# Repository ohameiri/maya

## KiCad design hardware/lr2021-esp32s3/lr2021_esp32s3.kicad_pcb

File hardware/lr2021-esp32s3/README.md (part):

# LR2021 + ESP32-S3 LoRa Plus board

A 4-layer, 62 × 47 mm KiCad 9 board with:

- **Semtech LR2021** LoRa Plus transceiver (QFN-32 5×5). Its matching networks follow Semtech's LR2021 reference design (switchless "direct-tie").
  - Sub-GHz path **868/915 MHz**, up to **+22 dBm** (PA_LF), on SMA **J5**.
  - **2.4 GHz** path, up to **+12 dBm** (PA_HF), on SMA **J6**.
- **ESP32-S3-WROOM-1U-N16R8** module (16 MB flash, 8 MB octal PSRAM, LCSC C3013946). This is the U.FL variant with no PCB antenna, so the board needs no antenna keepout. Wi-Fi/BLE are not used; the U.FL is left unconnected (an antenna can still be clipped on later if needed).
- **USB-C** wired straight to the ESP32-S3 native USB (GPIO19/20). It handles flashing, USB-CDC console and JTAG, with no USB-UART bridge.
- Power from **USB-C 5 V**, a **5 V screw terminal** or a **3.3 V screw terminal**. Any combination can be connected at the same time.
- RESET and BOOT buttons, a power LED, a user LED on GPIO2, and a 2×10 GPIO header.

Everything is generated from the Python scripts in [`scripts/`](scripts), so the design can be reviewed and rebuilt from source.

| | |
|---|---|
|  |  |

### 3D

| | |
|---|---|
|  |  |

The KiCad library has no 3D models for the HRO TYPE-C-31-M-12 USB-C receptacle, the XKB TS-1187A buttons or a 0402 diode. Simplified models built from the datasheet dimensions are generated by [`scripts/gen_3d_models.py`](scripts/gen_3d_models.py) (CadQuery) into `lib/3d/`, and the footprints point to them.

## Power design

### Load budget (from the datasheets)

| Consumer | Typical | Peak | Source |
|---|---|---|---|
| ESP32-S3 (Wi-Fi TX 802.11b, 20.5 dBm; worst case only, the radio is unused) | 95 mA (RX/idle) | **355 mA** | ESP32-S3-WROOM-1/1U datasheet |
| LR2021 TX PA_LF +22 dBm, 915 MHz (SIMO, 3.3 V) | 105 mA | **~120 mA** | LR2021 DS rev 1.1, IDDTXLF1 / Fig 1-3 |
| LR2021 TX PA_HF +12 dBm, 2.4 GHz | 24 mA | 24 mA | LR2021 DS Fig 1-7 |
| LEDs, pull-ups | 3 mA | 3 mA | |
| **Total on +3V3** | ~200 mA | **~480 mA** | |

The 3.3 V rail is sized for **1 A**, about 2× the worst-case peak.

### Topology

```
USB-C VBUS ──B5819W──┐
                     ├── +5V ── AP7361C-33 (1 A LDO) ── +3V3_LDO ── LM66100 ──┐
5V screw terminal ───┴──B5819W (SMF5.0CA TVS on input)                        ├── +3V3 ── ESP32-S3, LR2021 (via ferrite), LEDs
3V3 screw terminal ── +3V3_EXT ───────────────────────────────── LM66100 ──────┘
```

- **5 V inputs**: USB-C and the 5 V terminal are combined by two B5819W Schottky diodes. They block back-feed into the USB host and protect against reverse polarity. The LDO input then sees about 4.5 V.
- **LDO**: Diodes AP7361C-33E (1 A, 340 mV dropout at 1 A, SOT-223 with the GND tab on a ground pour). Worst-case dissipation is (4.55 − 3.3) V × 0.48 A ≈ 0.6 W during short Wi-Fi bursts. The average is about 0.15 W.
- **3.3 V inputs**: The LDO output and the external 3.3 V input are combined by two **TI LM66100** ideal diodes (CE tied to VOUT, the reverse-current-blocking setup in the TI datasheet).
  - The higher source supplies the rail and neither source can back-feed the other.
  - The drop is about 50 mV at 0.5 A (79–125 mΩ), so a 3.3 V input still gives at least 3.2 V.
  - The LM66100 also provides reverse-polarity protection on the 3.3 V terminal.
- **External 3.3 V must stay between 3.0 and 3.6 V.** The ESP32-S3 limit is 3.6 V and the LR2021 operating maximum is 3.7 V (absolute maximum 3.9 V).
- **LR2021 supply**: VBAT gets its own ferrite (FB1) plus 100 nF and 4.7 µF. The internal SIMO DC-DC uses the 2.2 µH LQM18PN2R2 inductor, as Semtech specifies. PA_LF reaches the full +22 dBm for VBAT ≥ 2.2 V.

The schematic has one intentional ERC warning: the two LM66100 outputs (power-out pins) are tied together. The project's pin-conflict matrix downgrades power-out↔power-out from error to warning for that reason.

## RF design

- **Matching values** come from Semtech's LR2021 reference design (e788v01a, 868/915 MHz + 2.4 GHz). PA chokes: 12 nH (LF) and 18 nH (HF). Values on the schematic RF sheet:
  - LF: L 4.7 nH, C 22 pF, C 7.5 pF ∥ (3.9 nH ∥ 1.8 pF), 3.9 pF, 2.4 nH, 1.8 pF.
  - LF RX: 18 pF, 2.2 pF, 24 nH.
  - HF: 1.5 nH, 6.8 pF, 2.7 pF, (1.6 nH ∥ 1.1 pF), 1.2 pF, 1.1 nH, 2.0 pF.
  - HF RX: 18 pF, 2.4 nH.
- **Antenna ESD (D6, D7)**: DOWO PESD0402V12 (LCSC C19626255) on each SMA feed, as in Semtech's reference design. It is 0.05 pF, bidirectional, with a 12 V working voltage, so it does not clip the +22 dBm signal: 4 V peak into 50 Ω, up to about 8 V into a badly matched antenna. Simulated insertion loss is 0.04–0.05 dB.
- **Optional parts (DNP)**: L12 and C33 are tuning pads.
- **Transmission lines**: grounded coplanar waveguide on L1 referenced to the solid **In1 ground plane**. Trace **0.38 mm** with a **0.2 mm** gap gives ≈ 50 Ω on the JLCPCB `JLC04161H-7628` stackup (0.2104 mm prepreg, εr ≈ 4.4).
  - A GND via fence runs along both sides of each feed, with gaps of 1.0–2.4 mm on the long runs (λ/20 at 2.45 GHz is 3.4 mm). [`add_rf_fence.py`](scripts/add_rf_fence.py) adds it after routing, and more stitching vias surround each SMA launch.
- **Layout**: The LR2021 is rotated so all its RF pins face the right board edge. Each band has a TX row and an RX row of 0402 parts, the same structure as Semtech's layout.
  - Shunt parts have their own ground via right at the pad.
  - The RF section was routed by hand and locked. The autorouter was fenced out of it.
- **ESP32 radio**: The WROOM-1U has no PCB antenna, so there is no keepout and the module sits inside the board. With Wi-Fi/BLE disabled in firmware the ESP32 draws about 30–40 mA; the supply is still sized for the radio-on worst case.

> **Tuning note.** Semtech's values were tuned on their own PCB with mostly 0201 parts. This board uses 0402 parts and a different layout, so the match is a good starting point, not a guarantee. Before running full power, check S11 and the TX output with a VNA or spectrum analyzer, and adjust the shunt capacitors if needed.

## ESP32-S3 ↔ LR2021 pin map

| LR2021 | ESP32-S3 | Notes |
|---|---|---|
| NSS | GPIO10 | 10 k pull-up (radio deselected during boot) |
| MOSI | GPIO11 | FSPI IO-MUX pins |
| SCK | GPIO12 | |
| MISO | GPIO13 | |
| NRESET | GPIO14 | |
| BUSY | GPIO21 | |
| DIO9 | GPIO47 | IRQ (map any LR2021 interrupt to it with `SetDioFunction`) |

Only one IRQ line is wired. RadioLib's LR2021 driver needs only an IRQ line plus BUSY.
- DIO5–DIO8, DIO10 and DIO11 are left unconnected. Semtech says unused DIOs can float. The switchless RF design needs no RF-switch control lines.
- Freeing those pins left room around the QFN for a clean hand fanout.

Other ESP32-S3 connections:
- USB D−/D+ go to GPIO19/20 (with USBLC6-2SC6 ESD protection).
- The user LED is on GPIO2. BOOT is GPIO0 and RESET is EN.
- GPIO header J4:

  | Pins | Signals |
  |---|---|
  | 1, 2 | 3V3, 5V |
  | 3–14 | GPIO4, 5, 6, 7, 9, 48, 38, 39, 40, 41, 42, 1 |
  | 15, 16 | U0TXD, U0RXD |
  | 17–20 | GND |

- Not used:
  - GPIO35–37 are taken by the octal PSRAM.
  - The strapping pins GPIO3, GPIO45 and GPIO46 are left free.
  - GPIO8 and GPIO15–18 are unconnected. On the compact board there is no room to route them from the module's left side to the header.

## PCB

- **Size and stackup**: 62 × 47 mm, 4 layers, 1.6 mm, JLCPCB `JLC04161H-7628`.
- **Mounting**: two M2 holes, one on the right edge between the two SMA connectors and one at the top between the ESP32 module and the radio section.

  | Layer | Use |
  |---|---|
  | L1 (F.Cu) | Components, RF, signals, GND pour |
  | L2 (In1) | Solid GND (RF reference) |
  | L3 (In2) | +3V3 plane |
  | L4 (B.Cu) | Signals, GND pour |

- **Hand-routed in [`gen_pcb.py`](scripts/gen_pcb.py)** and locked before autorouting:
  - the RF section;
  - the full LR2021 fanout (crystal, NTC divider, SIMO loop, VBAT/VDCC/VPAX, SPI escape vias);
  - the duplicated USB-C pads;
  - a via from every +3V3/GND pad to its plane.
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
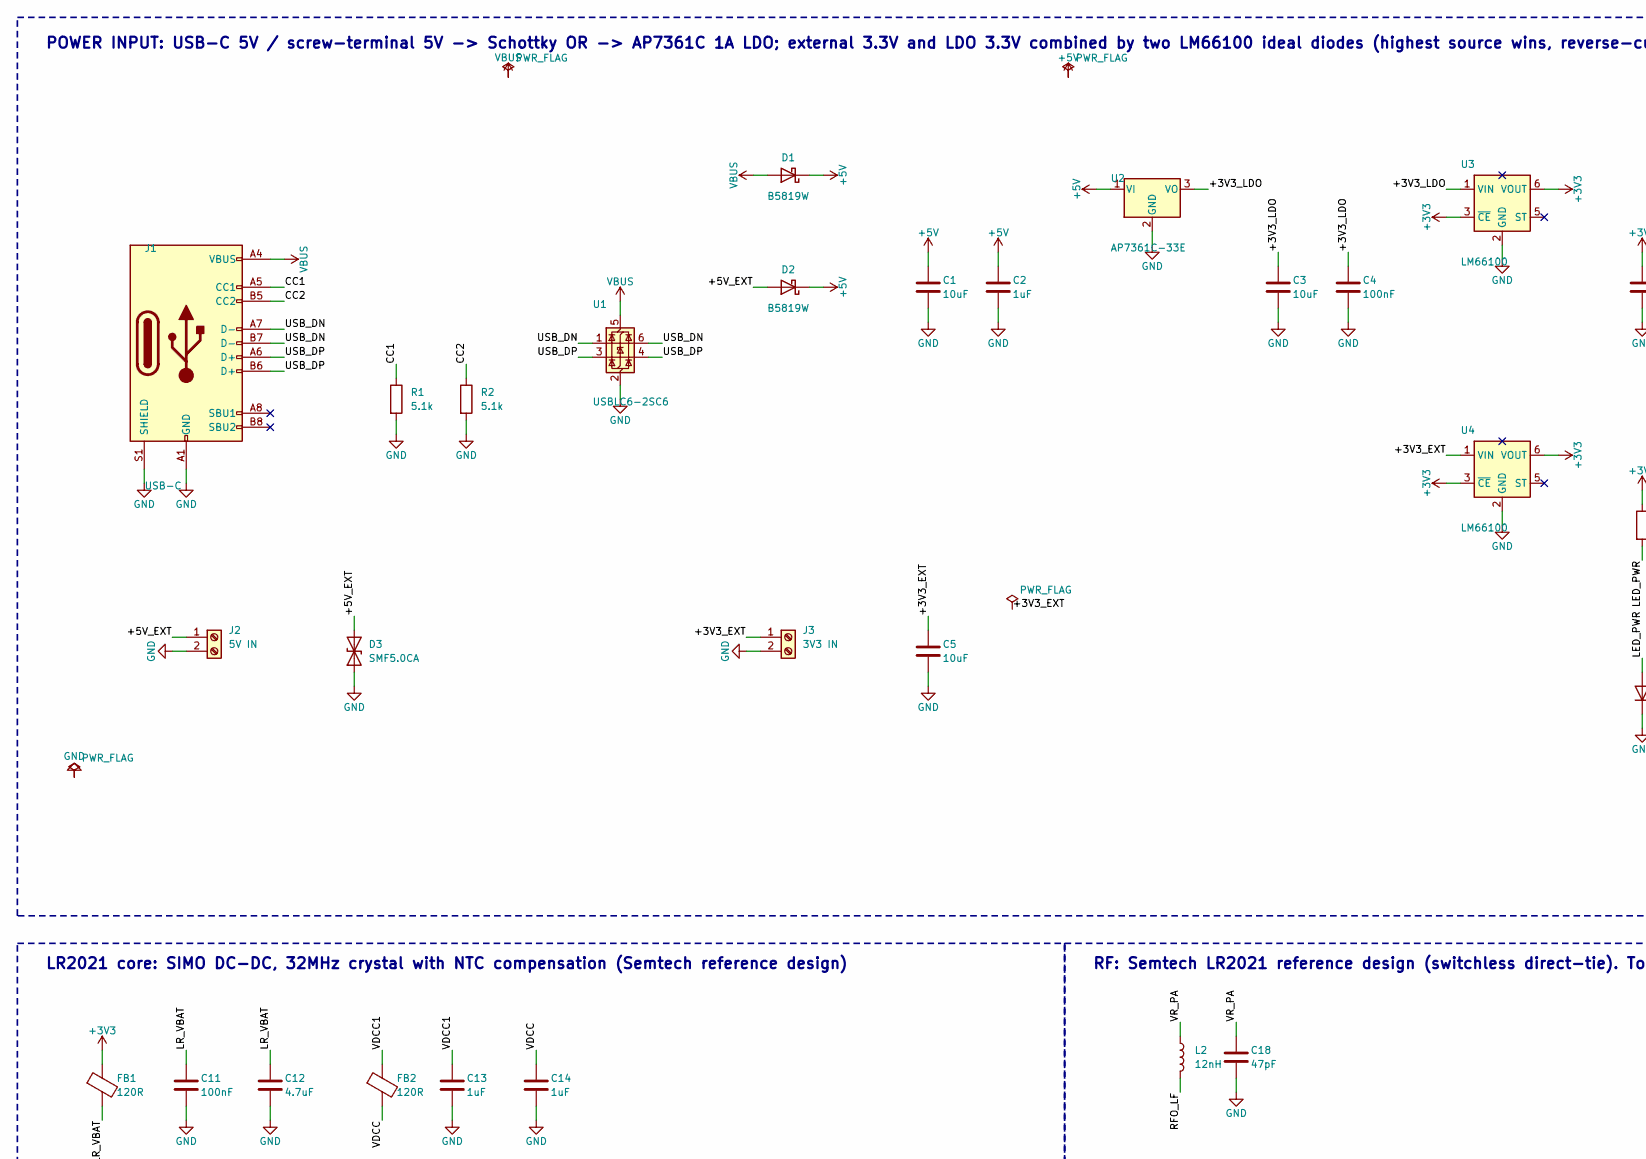
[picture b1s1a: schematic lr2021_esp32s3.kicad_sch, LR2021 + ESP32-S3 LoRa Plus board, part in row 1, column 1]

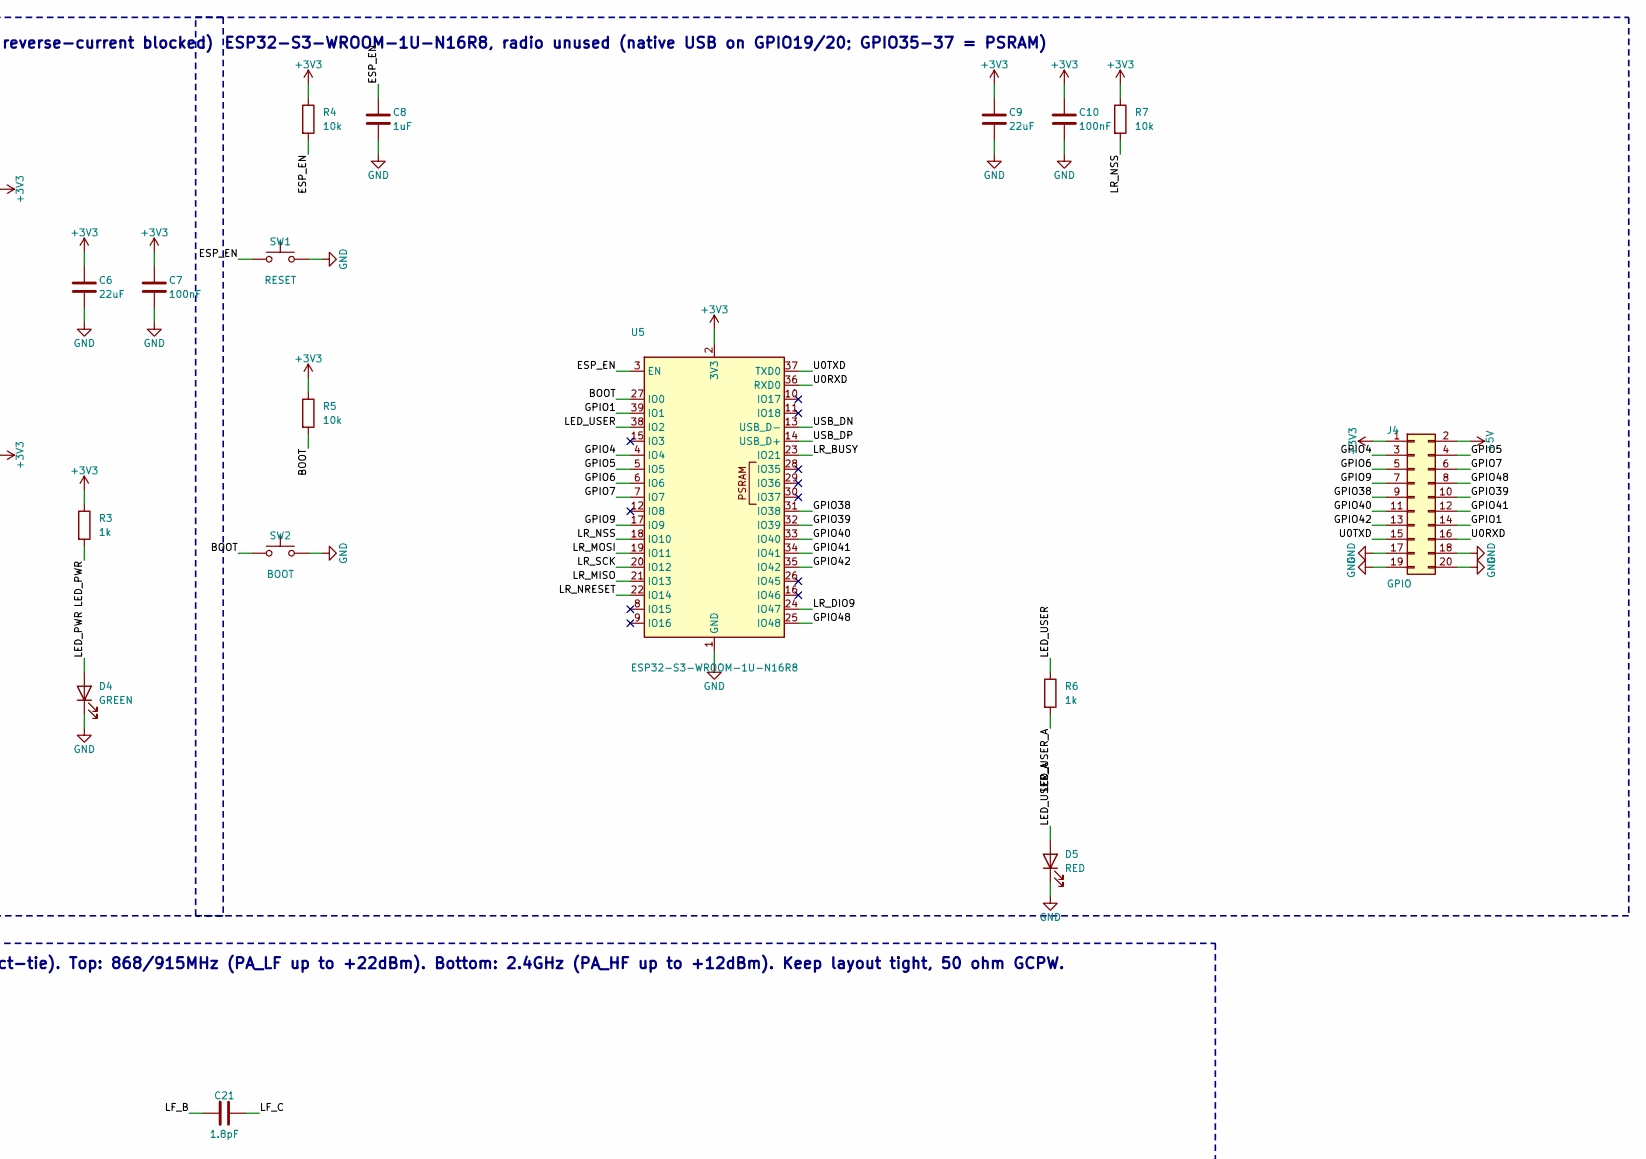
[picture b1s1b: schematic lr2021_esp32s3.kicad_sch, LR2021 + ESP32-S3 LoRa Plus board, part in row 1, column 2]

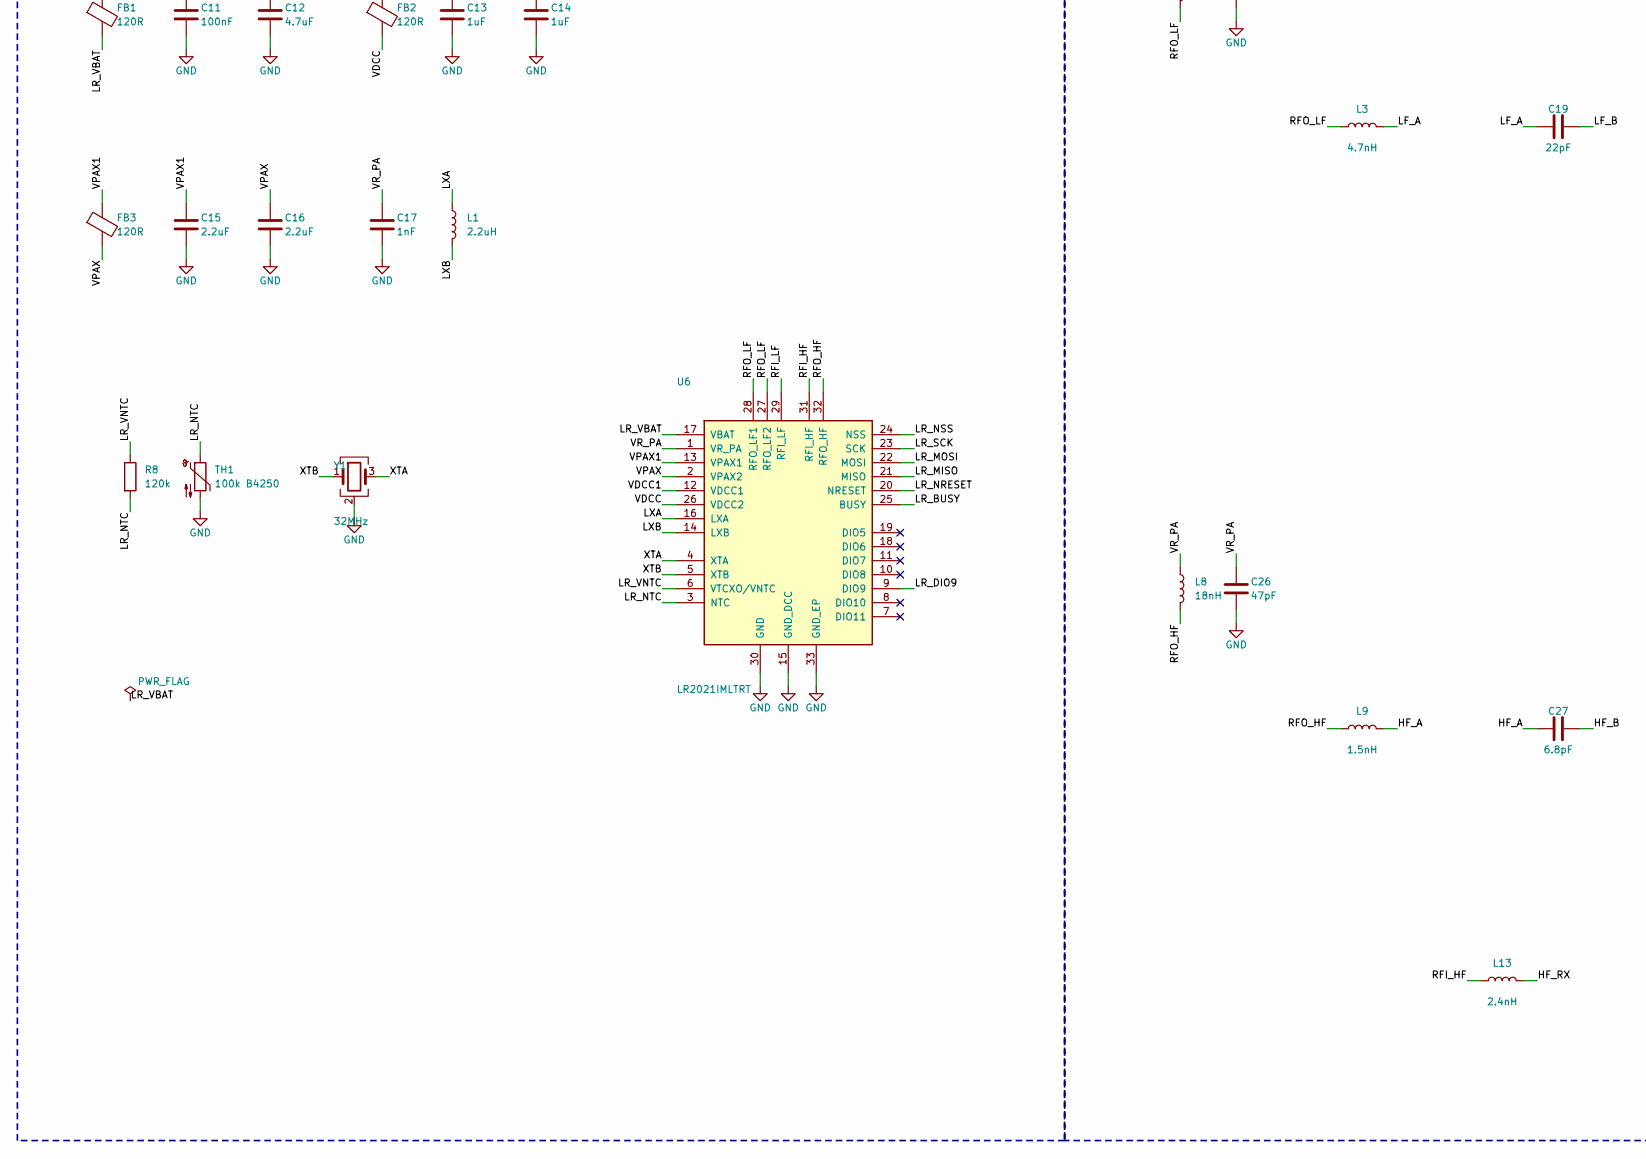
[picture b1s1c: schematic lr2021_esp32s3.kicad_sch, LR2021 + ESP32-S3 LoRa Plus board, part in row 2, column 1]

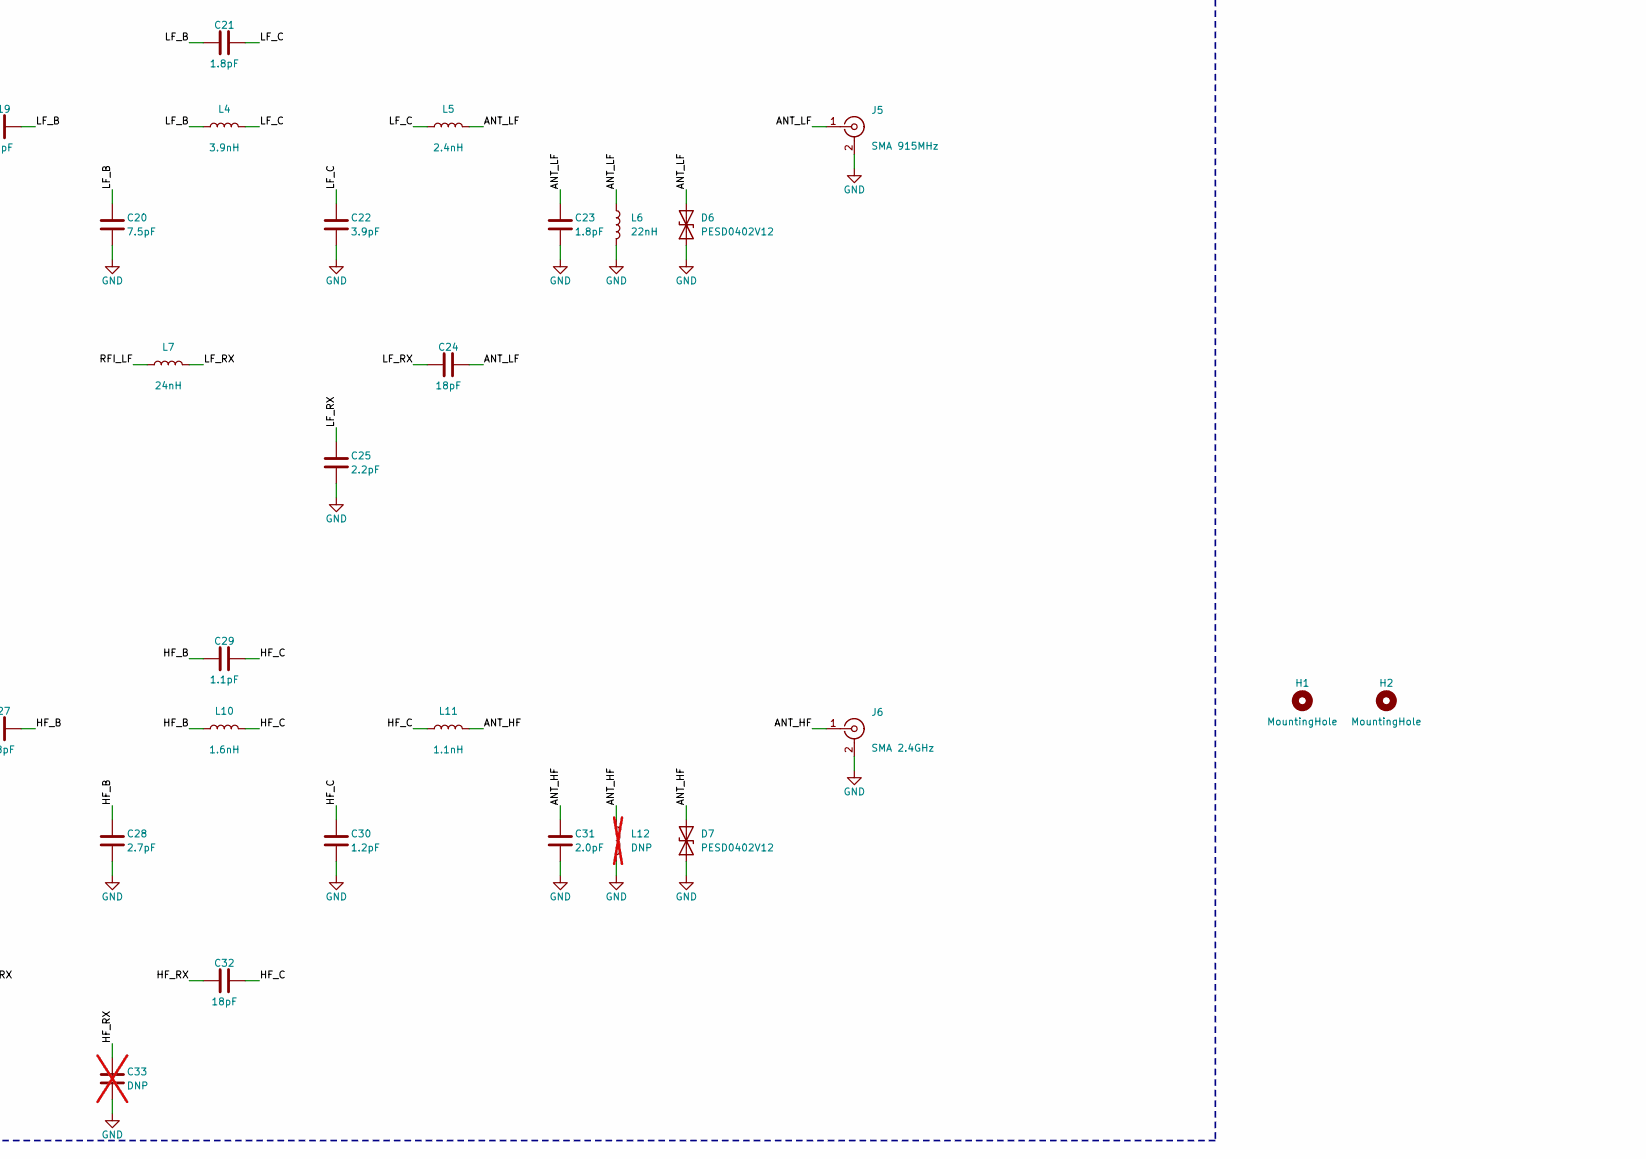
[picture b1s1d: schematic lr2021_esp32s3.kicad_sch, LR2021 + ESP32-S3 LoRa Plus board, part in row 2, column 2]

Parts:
C1, C3, C5: 10uF; C_0805_2012Metric; MPN CL21A106KAYNNNE; LCSC C15850
C2, C8, C13, C14: 1uF; C_0402_1005Metric; MPN CL05A105KA5NQNC; LCSC C52923
C4, C7, C10, C11: 100nF; C_0402_1005Metric; MPN CL05B104KO5NNNC; LCSC C1525
C6, C9: 22uF; C_0805_2012Metric; MPN CL21A226MAQNNNE; LCSC C45783
C12: 4.7uF; C_0402_1005Metric; MPN CL05A475MP5NRNC; LCSC C23733
C15, C16: 2.2uF; C_0402_1005Metric; MPN CL05A225KP5NSNC; LCSC C107369
C17: 1nF; C_0402_1005Metric; MPN 0402B102K500NT; LCSC C1523
C18, C26: 47pF; C_0402_1005Metric; MPN CC0402JRNPO9BN470; LCSC C60137
C19: 22pF; C_0402_1005Metric; MPN 0402CG220J500NT; LCSC C1555
C20: 7.5pF; C_0402_1005Metric; MPN CQ0402BRNPO9BN7R5; LCSC C1855318
C21, C23: 1.8pF; C_0402_1005Metric; MPN CC0402BRNPO9BN1R8; LCSC C327209
C22: 3.9pF; C_0402_1005Metric; MPN CC0402BRNPO9BN3R9; LCSC C505474
C24, C32: 18pF; C_0402_1005Metric; MPN 0402CG180J500NT; LCSC C1549
C25: 2.2pF; C_0402_1005Metric; MPN CC0402BRNPO9BN2R2; LCSC C325452
C27: 6.8pF; C_0402_1005Metric; MPN CC0402BRNPO9BN6R8; LCSC C327291
C28: 2.7pF; C_0402_1005Metric; MPN CC0402BRNPO9BN2R7; LCSC C326937
C29: 1.1pF; C_0402_1005Metric; MPN RF15N1R1B500CT; LCSC C180259
C30: 1.2pF; C_0402_1005Metric; MPN CC0402BRNPO9BN1R2; LCSC C327292
C31: 2.0pF; C_0402_1005Metric; MPN CC0402BRNPO9BN2R0; LCSC C281756
C33: DNP; C_0402_1005Metric; not fitted
D1, D2: B5819W; D_SOD-123; MPN B5819W; LCSC C8598
D3: SMF5.0CA; D_SOD-123F; MPN SMF5.0CA; LCSC C2980402
D4: GREEN; LED_0603_1608Metric; MPN LTST-C190KGKT; LCSC C125094
D5: RED; LED_0603_1608Metric; MPN KT-0603R; LCSC C2286
D6, D7: PESD0402V12; D_0402_1005Metric; MPN PESD0402V12; LCSC C19626255
FB1, FB2, FB3: 120R; L_0402_1005Metric; MPN BLM15AG121SN1D; LCSC C85812
H1, H2: MountingHole; MountingHole_2.2mm_M2
J1: USB-C; USB_C_Receptacle_HRO_TYPE-C-31-M-12; MPN HRO TYPE-C-31-M-12; LCSC C165948
J2: 5V IN; TerminalBlock_Phoenix_MKDS-1,5-2_1x02_P5.00mm_Horizontal; MPN KF301-5.0-2P; LCSC C474881
J3: 3V3 IN; TerminalBlock_Phoenix_MKDS-1,5-2_1x02_P5.00mm_Horizontal; MPN KF301-5.0-2P; LCSC C474881
J4: GPIO; PinHeader_2x10_P2.54mm_Vertical; MPN HX PZ2.54-2x10P ZZ; LCSC C42372518
J5: SMA 915MHz; SMA_Samtec_SMA-J-P-H-ST-EM1_EdgeMount; MPN SMA-J-P-H-ST-EM1; LCSC C5199907
J6: SMA 2.4GHz; SMA_Samtec_SMA-J-P-H-ST-EM1_EdgeMount; MPN SMA-J-P-H-ST-EM1; LCSC C5199907
L1: 2.2uH; L_0603_1608Metric; MPN LQM18PN2R2MFRL; LCSC C337910
L2: 12nH; L_0402_1005Metric; MPN LQW15AN12NG00D; LCSC C86128
L3: 4.7nH; L_0402_1005Metric; MPN LQW15AN4N7B00D; LCSC C98064
L4: 3.9nH; L_0402_1005Metric; MPN LQW15AN3N9B00D; LCSC C98062
L5, L13: 2.4nH; L_0402_1005Metric; MPN LQW15AN2N4B00D; LCSC C113113
L6: 22nH; L_0402_1005Metric; MPN LQW15AN22NG00D; LCSC C86129
L7: 24nH; L_0402_1005Metric; MPN LQW15AN24NG00D; LCSC C167472
L8: 18nH; L_0402_1005Metric; MPN LQW15AN18NG00D; LCSC C91622
L9: 1.5nH; L_0402_1005Metric; MPN LQW15AN1N5B00D; LCSC C18221
L10: 1.6nH; L_0402_1005Metric; MPN MWSD1005C1N6STM01; LCSC C778760
L11: 1.1nH; L_0402_1005Metric; MPN MHQ1005P1N1BT000; LCSC C1332701
L12: DNP; L_0402_1005Metric; not fitted
R1, R2: 5.1k; R_0402_1005Metric; MPN 0402WGF5101TCE; LCSC C25905
R3, R6: 1k; R_0402_1005Metric; MPN 0402WGF1001TCE; LCSC C11702
R4, R5, R7: 10k; R_0402_1005Metric; MPN 0402WGF1002TCE; LCSC C25744
R8: 120k; R_0402_1005Metric; MPN 0402WGF1203TCE; LCSC C25750
SW1: RESET; SW_Push_1P1T_XKB_TS-1187A; MPN TS-1187A-B-A-B; LCSC C318884
SW2: BOOT; SW_Push_1P1T_XKB_TS-1187A; MPN TS-1187A-B-A-B; LCSC C318884
TH1: 100k B4250; R_0402_1005Metric; MPN NCP15WF104F03RC; LCSC C77130
U1: USBLC6-2SC6; SOT-23-6; MPN USBLC6-2SC6; LCSC C7519
U2: AP7361C-33E; SOT-223-3_TabPin2; MPN AP7361C-33E-13; LCSC C500795
U3, U4: LM66100; SOT-363_SC-70-6; MPN LM66100DCKR; LCSC C2869734
U5: ESP32-S3-WROOM-1U-N16R8; ESP32-S3-WROOM-1U; MPN ESP32-S3-WROOM-1U-N16R8; LCSC C3013946
U6: LR2021IMLTRT; QFN-32-1EP_5x5mm_P0.5mm_EP3.7x3.7mm_ThermalVias; MPN LR2021IMLTRT; LCSC C49421489
Y1: 32MHz; Crystal_SMD_2016-4Pin_2.0x1.6mm; MPN NX2016SA-32M-EXS00A-CS06465; LCSC C1986260

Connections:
+3V3: C6.1, C7.1, C9.1, C10.1, FB1.1, J4.1, R3.1, R4.1, R5.1, R7.1, U3.3 (~CE), U3.6 (VOUT), U4.3 (~CE), U4.6 (VOUT), U5.2 (3V3)
+5V: C1.1, C2.1, D1.1 (K), D2.1 (K), J4.2, U2.1 (VI)
/+3V3_EXT: C5.1, J3.1, U4.1 (VIN)
/+3V3_LDO: C3.1, C4.1, U2.3 (VO), U3.1 (VIN)
/+5V_EXT: D2.2 (A), D3.2 (A2), J2.1
/ANT_HF: C31.1, D7.2 (A2), J6.1 (In), L11.2, L12.1
/ANT_LF: C23.1, C24.2, D6.2 (A2), J5.1 (In), L5.2, L6.1
/BOOT: R5.2, SW2.1, U5.27 (IO0)
/CC1: J1.A5 (CC1), R1.1
/CC2: J1.B5 (CC2), R2.1
/ESP_EN: C8.1, R4.2, SW1.1, U5.3 (EN)
/GPIO1: J4.14, U5.39 (IO1)
/GPIO4: J4.3, U5.4 (IO4)
/GPIO5: J4.4, U5.5 (IO5)
/GPIO6: J4.5, U5.6 (IO6)
/GPIO7: J4.6, U5.7 (IO7)
/GPIO9: J4.7, U5.17 (IO9)
/GPIO38: J4.9, U5.31 (IO38)
/GPIO39: J4.10, U5.32 (IO39)
/GPIO40: J4.11, U5.33 (IO40)
/GPIO41: J4.12, U5.34 (IO41)
/GPIO42: J4.13, U5.35 (IO42)
/GPIO48: J4.8, U5.25 (IO48)
/HF_A: C27.1, L9.2
/HF_B: C27.2, C28.1, C29.1, L10.1
/HF_C: C29.2, C30.1, C32.2, L10.2, L11.1
/HF_RX: C32.1, C33.1, L13.2
/LED_PWR: D4.2 (A), R3.2
/LED_USER: R6.1, U5.38 (IO2)
/LED_USER_A: D5.2 (A), R6.2
/LF_A: C19.1, L3.2
/LF_B: C19.2, C20.1, C21.1, L4.1
/LF_C: C21.2, C22.1, L4.2, L5.1
/LF_RX: C24.1, C25.1, L7.2
/LR_BUSY: U5.23 (IO21), U6.25 (BUSY)
/LR_DIO9: U5.24 (IO47), U6.9 (DIO9)
/LR_MISO: U5.21 (IO13), U6.21 (MISO)
/LR_MOSI: U5.19 (IO11), U6.22 (MOSI)
/LR_NRESET: U5.22 (IO14), U6.20 (NRESET)
/LR_NSS: R7.2, U5.18 (IO10), U6.24 (NSS)
/LR_NTC: R8.2, TH1.1, U6.3 (NTC)
/LR_SCK: U5.20 (IO12), U6.23 (SCK)
/LR_VBAT: C11.1, C12.1, FB1.2, U6.17 (VBAT)
/LR_VNTC: R8.1, U6.6 (VTCXO/VNTC)
/LXA: L1.1, U6.16 (LXA)
/LXB: L1.2, U6.14 (LXB)
/RFI_HF: L13.1, U6.31 (RFI_HF)
/RFI_LF: L7.1, U6.29 (RFI_LF)
/RFO_HF: L8.2, L9.1, U6.32 (RFO_HF)
/RFO_LF: L2.2, L3.1, U6.27 (RFO_LF2), U6.28 (RFO_LF1)
/U0RXD: J4.16, U5.36 (RXD0)
/U0TXD: J4.15, U5.37 (TXD0)
/USB_DN: J1.A7 (D-), J1.B7 (D-), U1.1 (I/O1), U1.6 (I/O1), U5.13 (USB_D-)
/USB_DP: J1.A6 (D+), J1.B6 (D+), U1.3 (I/O2), U1.4 (I/O2), U5.14 (USB_D+)
/VDCC: C14.1, FB2.2, U6.26 (VDCC2)
/VDCC1: C13.1, FB2.1, U6.12 (VDCC1)
/VPAX: C16.1, FB3.2, U6.2 (VPAX2)
/VPAX1: C15.1, FB3.1, U6.13 (VPAX1)
/VR_PA: C17.1, C18.1, C26.1, L2.1, L8.1, U6.1 (VR_PA)
/XTA: U6.4 (XTA), Y1.3
/XTB: U6.5 (XTB), Y1.1
GND: C1.2, C2.2, C3.2, C4.2, C5.2, C6.2, C7.2, C8.2, C9.2, C10.2, C11.2, C12.2, C13.2, C14.2, C15.2, C16.2, C17.2, C18.2, C20.2, C22.2, C23.2, C25.2, C26.2, C28.2, C30.2, C31.2, C33.2, D3.1 (A1), D4.1 (K), D5.1 (K), D6.1 (A1), D7.1 (A1), J1.A1 (GND), J1.A12 (GND), J1.B1 (GND), J1.B12 (GND), J1.S1 (SHIELD), J2.2, J3.2, J4.17, J4.18, J4.19, J4.20, J5.2 (Ext), J6.2 (Ext), L6.2, L12.2, R1.2, R2.2, SW1.2, SW2.2, TH1.2, U1.2 (GND), U2.2 (GND), U3.2 (GND), U4.2 (GND), U5.1 (GND), U5.40 (GND), U5.41 (GND), U6.15 (GND_DCC), U6.30 (GND), U6.33 (GND_EP), Y1.2 (G), Y1.4 (G)
VBUS: D1.2 (A), J1.A4 (VBUS), J1.A9 (VBUS), J1.B4 (VBUS), J1.B9 (VBUS), U1.5 (VBUS)

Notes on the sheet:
POWER INPUT: USB-C 5V / screw-terminal 5V -> Schottky OR -> AP7361C 1A LDO; external 3.3V and LDO 3.3V combined by two LM66100 ideal diodes (highest source wins, reverse-current blocked)
ESP32-S3-WROOM-1U-N16R8, radio unused (native USB on GPIO19/20; GPIO35-37 = PSRAM)
LR2021 core: SIMO DC-DC, 32MHz crystal with NTC compensation (Semtech reference design)
RF: Semtech LR2021 reference design (switchless direct-tie). Top: 868/915MHz (PA_LF up to +22dBm). Bottom: 2.4GHz (PA_HF up to +12dBm). Keep layout tight, 50 ohm GCPW.

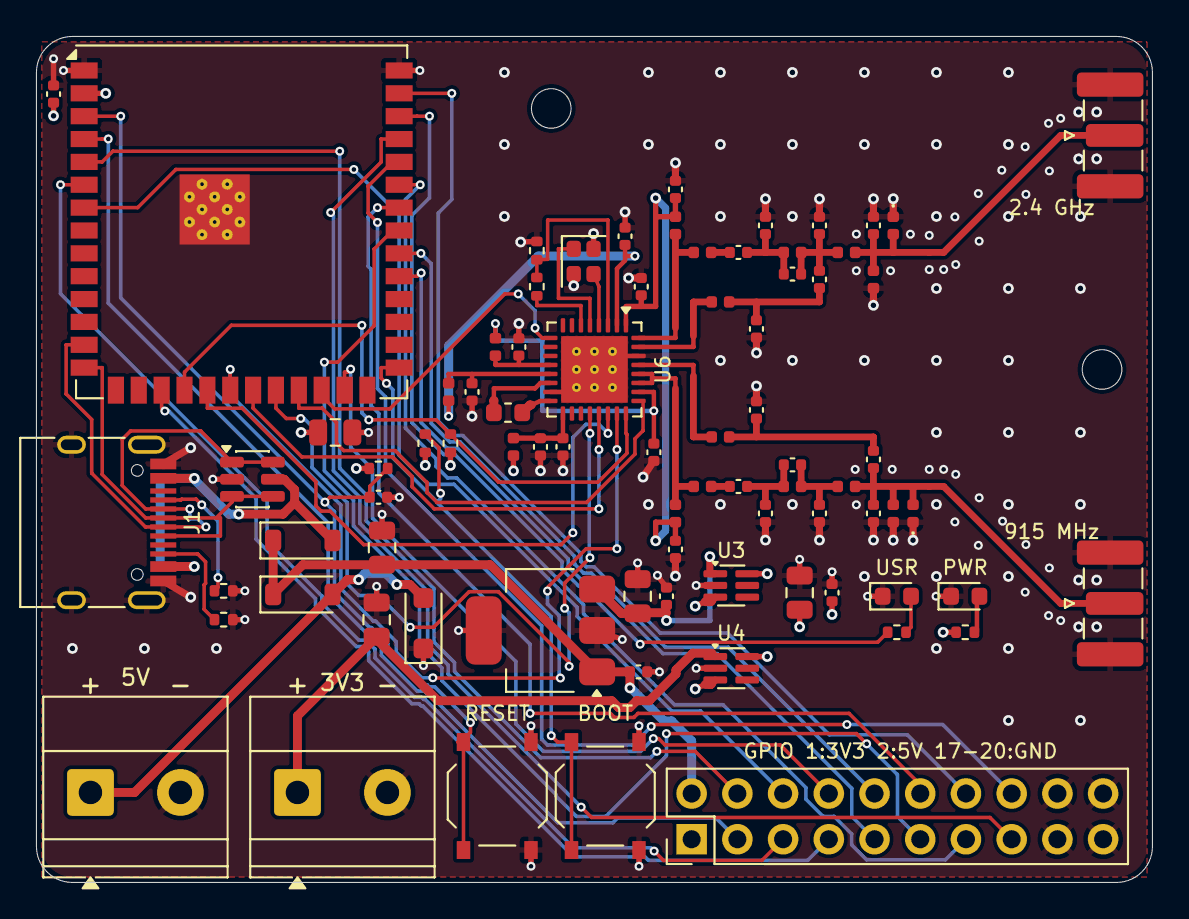
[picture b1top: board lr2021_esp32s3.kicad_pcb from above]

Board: 4 copper layers, 62.0 x 47.0 mm, 82 parts (0 on the bottom side), 63 nets.

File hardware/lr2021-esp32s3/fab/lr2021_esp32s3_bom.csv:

Qty,References,Value,Description,Footprint,MPN,LCSC,Notes,Populate
3,C1 C3 C5,10uF,10uF 16V X5R 0805,C_0805_2012Metric,CL21A106KAYNNNE,C15850,,yes
4,C2 C8 C13 C14,1uF,1uF 10V X5R 0402,C_0402_1005Metric,CL05A105KA5NQNC,C52923,,yes
4,C4 C7 C10 C11,100nF,100nF 16V X7R 0402,C_0402_1005Metric,CL05B104KO5NNNC,C1525,,yes
2,C6 C9,22uF,22uF 16V X5R 0805,C_0805_2012Metric,CL21A226MAQNNNE,C45783,,yes
1,C12,4.7uF,4.7uF 10V X5R 0402,C_0402_1005Metric,CL05A475MP5NRNC,C23733,,yes
2,C15 C16,2.2uF,2.2uF 10V X5R 0402,C_0402_1005Metric,CL05A225KP5NSNC,C107369,,yes
1,C17,1nF,1nF 16V X7R 0402,C_0402_1005Metric,0402B102K500NT,C1523,,yes
2,C18 C26,47pF,47pF 50V C0G/NP0 0402,C_0402_1005Metric,CC0402JRNPO9BN470,C60137,"C0G/NP0, +/-0.1pF (<10pF) or 2%, Murata GRM15/GJM15 high-Q",yes
1,C19,22pF,22pF 50V C0G/NP0 0402,C_0402_1005Metric,0402CG220J500NT,C1555,"C0G/NP0, +/-0.1pF (<10pF) or 2%, Murata GRM15/GJM15 high-Q",yes
1,C20,7.5pF,7.5pF 50V C0G/NP0 0402,C_0402_1005Metric,CQ0402BRNPO9BN7R5,C1855318,"C0G/NP0, +/-0.1pF (<10pF) or 2%, Murata GRM15/GJM15 high-Q",yes
2,C21 C23,1.8pF,1.8pF 50V C0G/NP0 0402,C_0402_1005Metric,CC0402BRNPO9BN1R8,C327209,"C0G/NP0, +/-0.1pF (<10pF) or 2%, Murata GRM15/GJM15 high-Q",yes
1,C22,3.9pF,3.9pF 50V C0G/NP0 0402,C_0402_1005Metric,CC0402BRNPO9BN3R9,C505474,"C0G/NP0, +/-0.1pF (<10pF) or 2%, Murata GRM15/GJM15 high-Q",yes
2,C24 C32,18pF,18pF 50V C0G/NP0 0402,C_0402_1005Metric,0402CG180J500NT,C1549,"C0G/NP0, +/-0.1pF (<10pF) or 2%, Murata GRM15/GJM15 high-Q",yes
1,C25,2.2pF,2.2pF 50V C0G/NP0 0402,C_0402_1005Metric,CC0402BRNPO9BN2R2,C325452,"C0G/NP0, +/-0.1pF (<10pF) or 2%, Murata GRM15/GJM15 high-Q",yes
1,C27,6.8pF,6.8pF 50V C0G/NP0 0402,C_0402_1005Metric,CC0402BRNPO9BN6R8,C327291,"C0G/NP0, +/-0.1pF (<10pF) or 2%, Murata GRM15/GJM15 high-Q",yes
1,C28,2.7pF,2.7pF 50V C0G/NP0 0402,C_0402_1005Metric,CC0402BRNPO9BN2R7,C326937,"C0G/NP0, +/-0.1pF (<10pF) or 2%, Murata GRM15/GJM15 high-Q",yes
1,C29,1.1pF,1.1pF 50V C0G/NP0 0402,C_0402_1005Metric,RF15N1R1B500CT,C180259,"C0G/NP0, +/-0.1pF (<10pF) or 2%, Murata GRM15/GJM15 high-Q",yes
1,C30,1.2pF,1.2pF 50V C0G/NP0 0402,C_0402_1005Metric,CC0402BRNPO9BN1R2,C327292,"C0G/NP0, +/-0.1pF (<10pF) or 2%, Murata GRM15/GJM15 high-Q",yes
1,C31,2.0pF,2.0pF 50V C0G/NP0 0402,C_0402_1005Metric,CC0402BRNPO9BN2R0,C281756,"C0G/NP0, +/-0.1pF (<10pF) or 2%, Murata GRM15/GJM15 high-Q",yes
1,C33,DNP,DNP 10V X5R 0402,C_0402_1005Metric,,,"C0G/NP0, +/-0.1pF (<10pF) or 2%, Murata GRM15/GJM15 high-Q",DNP
2,D1 D2,B5819W,B5819W,D_SOD-123,B5819W,C8598,,yes
1,D3,SMF5.0CA,SMF5.0CA,D_SOD-123F,SMF5.0CA,C2980402,,yes
1,D4,GREEN,GREEN,LED_0603_1608Metric,LTST-C190KGKT,C125094,,yes
1,D5,RED,RED,LED_0603_1608Metric,KT-0603R,C2286,,yes
2,D6 D7,PESD0402V12,PESD0402V12,D_0402_1005Metric,PESD0402V12,C19626255,"Antenna ESD, 0.05pF, bidirectional, Vrwm 12V (Semtech ref populates this)",yes
3,FB1 FB2 FB3,120R,120R,L_0402_1005Metric,BLM15AG121SN1D,C85812,,yes
1,J1,USB-C,USB-C,USB_C_Receptacle_HRO_TYPE-C-31-M-12,HRO TYPE-C-31-M-12,C165948,,yes
1,J2,5V IN,5V IN,"TerminalBlock_Phoenix_MKDS-1,5-2_1x02_P5.00mm_Horizontal",KF301-5.0-2P,C474881,,yes
1,J3,3V3 IN,3V3 IN,"TerminalBlock_Phoenix_MKDS-1,5-2_1x02_P5.00mm_Horizontal",KF301-5.0-2P,C474881,,yes
1,J4,GPIO,GPIO,PinHeader_2x10_P2.54mm_Vertical,HX PZ2.54-2x10P ZZ,C42372518,,yes
1,J5,SMA 915MHz,SMA 915MHz,SMA_Samtec_SMA-J-P-H-ST-EM1_EdgeMount,SMA-J-P-H-ST-EM1,C5199907,"SMA female edge mount, 1.6mm PCB",yes
1,J6,SMA 2.4GHz,SMA 2.4GHz,SMA_Samtec_SMA-J-P-H-ST-EM1_EdgeMount,SMA-J-P-H-ST-EM1,C5199907,"SMA female edge mount, 1.6mm PCB",yes
1,L1,2.2uH,2.2uH,L_0603_1608Metric,LQM18PN2R2MFRL,C337910,"SIMO inductor: DCR<0.5R, Isat>200mA, SRF>20MHz",yes
1,L2,12nH,12nH,L_0402_1005Metric,LQW15AN12NG00D,C86128,"Wire-wound high-Q, +/-2% or +/-0.1nH, Murata LQW15AN series",yes
1,L3,4.7nH,4.7nH,L_0402_1005Metric,LQW15AN4N7B00D,C98064,"Wire-wound high-Q, +/-2% or +/-0.1nH, Murata LQW15AN series",yes
1,L4,3.9nH,3.9nH,L_0402_1005Metric,LQW15AN3N9B00D,C98062,"Wire-wound high-Q, +/-2% or +/-0.1nH, Murata LQW15AN series",yes
2,L5 L13,2.4nH,2.4nH,L_0402_1005Metric,LQW15AN2N4B00D,C113113,"Wire-wound high-Q, +/-2% or +/-0.1nH, Murata LQW15AN series",yes
1,L6,22nH,22nH,L_0402_1005Metric,LQW15AN22NG00D,C86129,"Wire-wound high-Q, +/-2% or +/-0.1nH, Murata LQW15AN series",yes
1,L7,24nH,24nH,L_0402_1005Metric,LQW15AN24NG00D,C167472,"Wire-wound high-Q, +/-2% or +/-0.1nH, Murata LQW15AN series",yes
1,L8,18nH,18nH,L_0402_1005Metric,LQW15AN18NG00D,C91622,"Wire-wound high-Q, +/-2% or +/-0.1nH, Murata LQW15AN series",yes
1,L9,1.5nH,1.5nH,L_0402_1005Metric,LQW15AN1N5B00D,C18221,"Wire-wound high-Q, +/-2% or +/-0.1nH, Murata LQW15AN series",yes
1,L10,1.6nH,1.6nH,L_0402_1005Metric,MWSD1005C1N6STM01,C778760,"Wire-wound high-Q, +/-2% or +/-0.1nH, Murata LQW15AN series",yes
1,L11,1.1nH,1.1nH,L_0402_1005Metric,MHQ1005P1N1BT000,C1332701,"Wire-wound high-Q, +/-2% or +/-0.1nH, Murata LQW15AN series",yes
1,L12,DNP,DNP,L_0402_1005Metric,,,"Wire-wound high-Q, +/-2% or +/-0.1nH, Murata LQW15AN series",DNP
2,R1 R2,5.1k,5.1k 1% 0402,R_0402_1005Metric,0402WGF5101TCE,C25905,,yes
2,R3 R6,1k,1k 1% 0402,R_0402_1005Metric,0402WGF1001TCE,C11702,,yes
3,R4 R5 R7,10k,10k 1% 0402,R_0402_1005Metric,0402WGF1002TCE,C25744,,yes
1,R8,120k,120k 1% 0402,R_0402_1005Metric,0402WGF1203TCE,C25750,,yes
1,SW1,RESET,RESET,SW_Push_1P1T_XKB_TS-1187A,TS-1187A-B-A-B,C318884,,yes
1,SW2,BOOT,BOOT,SW_Push_1P1T_XKB_TS-1187A,TS-1187A-B-A-B,C318884,,yes
1,TH1,100k B4250,100k B4250,R_0402_1005Metric,NCP15WF104F03RC,C77130,,yes
1,U1,USBLC6-2SC6,USBLC6-2SC6,SOT-23-6,USBLC6-2SC6,C7519,,yes
1,U2,AP7361C-33E,AP7361C-33E,SOT-223-3_TabPin2,AP7361C-33E-13,C500795,,yes
2,U3 U4,LM66100,LM66100,SOT-363_SC-70-6,LM66100DCKR,C2869734,,yes
1,U5,ESP32-S3-WROOM-1U-N16R8,ESP32-S3-WROOM-1U-N16R8,ESP32-S3-WROOM-1U,ESP32-S3-WROOM-1U-N16R8,C3013946,,yes
1,U6,LR2021IMLTRT,LR2021IMLTRT,QFN-32-1EP_5x5mm_P0.5mm_EP3.7x3.7mm_ThermalVias,LR2021IMLTRT,C49421489,,yes
1,Y1,32MHz,32MHz,Crystal_SMD_2016-4Pin_2.0x1.6mm,NX2016SA-32M-EXS00A-CS06465,C1986260,"32MHz, CL=10pF, +/-10ppm, ESR<60R (2016)",yes

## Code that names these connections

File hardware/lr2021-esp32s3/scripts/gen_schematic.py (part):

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ESP_NETS = {
    '2': '+3V3', '1': 'GND', '40': 'GND', '41': 'GND', '3': 'ESP_EN', '27': 'BOOT',
    '13': 'USB_DN', '14': 'USB_DP',
    '17': 'GPIO9', '18': 'LR_NSS', '19': 'LR_MOSI', '20': 'LR_SCK', '21': 'LR_MISO', '22': 'LR_NRESET',
    '23': 'LR_BUSY', '24': 'LR_DIO9', '25': 'GPIO48', '12': NC, '38': 'LED_USER',
    '39': 'GPIO1', '4': 'GPIO4', '5': 'GPIO5', '6': 'GPIO6', '7': 'GPIO7', '8': NC, '9': NC,
    '10': NC, '11': NC, '31': 'GPIO38', '32': 'GPIO39', '33': 'GPIO40', '34': 'GPIO41',
    '35': 'GPIO42', '37': 'U0TXD', '36': 'U0RXD',
    '15': NC, '16': NC, '26': NC, '28': NC, '29': NC, '30': NC,
}
# WROOM-1U: same pinout as the WROOM-1 symbol, but no PCB antenna (u.FL connector left
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vres('R6', '1k', 480, 135, 'LED_USER', 'LED_USER_A')
part('D5', 'Device:LED', 'RED', 'LED_SMD:LED_0603_1608Metric', 480, 165, 90, {'2': 'LED_USER_A', '1': 'GND'})
vres('R7', '10k', 494, 30, '+3V3', 'LR_NSS')
HDR = {'1': '+3V3', '2': '+5V', '3': 'GPIO4', '4': 'GPIO5', '5': 'GPIO6', '6': 'GPIO7', '7': 'GPIO9', '8': 'GPIO48',
       '9': 'GPIO38', '10': 'GPIO39', '11': 'GPIO40', '12': 'GPIO41', '13': 'GPIO42', '14': 'GPIO1',
       '15': 'U0TXD', '16': 'U0RXD', '17': 'GND', '18': 'GND', '19': 'GND', '20': 'GND'}
part('J4', 'Connector_Generic:Conn_02x10_Odd_Even', 'GPIO', 'Connector_PinHeader_2.54mm:PinHeader_2x10_P2.54mm_Vertical',
     545, 100, 0, HDR)
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
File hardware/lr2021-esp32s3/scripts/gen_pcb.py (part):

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            self.track(net, [end, (xd, end[1]), (j[0] - 3.0, j[1]), j])
            feeds.append((end, xd, j))

        # ---- VR_PA: pin 1 -> C17 -> HF choke L8/C26; In2 link to the LF choke L2/C18
        l8, c26 = pp('L8', '/VR_PA'), pp('C26', '/VR_PA')
        self.track('/VR_PA', [pin(1), R(1.75, -3.5)], w=PIN_W)
        self.track('/VR_PA', [R(1.75, -3.5), R(3.4, -3.5), (UX + 3.4, l8[1]), l8], w=0.3)
        self.track('/VR_PA', [R(2.6, -3.5), pp('C17', '/VR_PA')], w=0.3)
        self.track('/VR_PA', [l8, c26], w=0.3)
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            p = pin(n)
            self.track('GND', [p, (UX + (p[0] - UX) * 0.6, p[1])], w=PIN_W)
        # VDCC2 escape between the chip and the LF riser
        self.track('/VDCC', [pin(26), R(3.3, 1.25), pp('C14', '/VDCC')], w=PIN_W)
        self.fanout_lr2021(pin)

        # Stitching vias along both sides of the antenna feeds and around the SMA launch
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
        # Top row: XTA straight up, XTB around the left of the crystal, VTCXO -> R8,
        # NTC over the top of the crystal to the divider, VPAX2 -> C16.
        self.track('/XTA', [pin(4), R(0.25, -4.6), pp('Y1', '/XTA')], w=0.2)
        self.track('/XTB', [pin(5), R(-0.25, -3.95), R(-2.0, -3.95), R(-2.0, -6.7), pp('Y1', '/XTB')], w=0.2)
        y1 = self.fps['Y1']
        for padnum, at in (('2', R(-1.15, -4.65)), ('4', R(-0.05, -7.55))):
            p = y1.FindPadByNumber(padnum).GetPosition()
            gnd('Y1', at, (pcbnew.ToMM(p.x), pcbnew.ToMM(p.y)))
        self.track('/LR_VNTC', [pin(6), R(-0.75, -3.55), R(-3.2, -3.55), pp('R8', '/LR_VNTC')], w=0.2)
        self.track('/LR_NTC', [pp('R8', '/LR_NTC'), pp('TH1', '/LR_NTC')], w=0.2)
        self.track('/LR_NTC', [pin(3), R(0.75, -8.3), R(-2.6, -8.3), R(-2.6, -6.12), pp('TH1', '/LR_NTC')], w=0.2)
        gnd('TH1', R(-4.1, -7.08))
        self.track('/VPAX', [pin(2), R(1.25, -5.6), R(1.7, -6.05), pp('C16', '/VPAX')], w=0.25)
        self.track('/VPAX', [R(1.7, -6.3), R(2.25, -6.3)], w=0.25)
        self.via('/VPAX', R(2.25, -6.3), *SV)
        gnd('C16', R(1.7, -8.75))
        # Left column: DIO9 to a via, VDCC1 / VPAX1 straight out to their caps and
        # ferrites, LXA/LXB down to the SIMO inductor, GND_DCC into the exposed pad.
        sig('/LR_DIO9', [pin(9), R(-2.9, -1.75), R(-3.3, -2.15), R(-3.3, -2.3)])
        self.track('/VDCC1', [pin(12), R(-5.5, -0.25)], w=0.25)
        for ref in ('C13', 'FB2'):
            p = pp(ref, '/VDCC1')
            self.track('/VDCC1', [(p[0], UY - 0.25), p], w=0.25)
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        # thermal vias and the bottom-row fanout vias, then up the left side.
        self.track('/VDCC', [R(3.3, 2.3), R(-2.9, 2.3), R(-2.9, -1.6), R(-5.5, -1.6), R(-5.5, -2.55)],
                   w=0.25, layer=pcbnew.B_Cu)
        self.track('/VPAX1', [pin(13), R(-8.1, 0.25)], w=0.25)
        for ref in ('C15', 'FB3'):
            p = pp(ref, '/VPAX1')
            self.track('/VPAX1', [(p[0], UY + 0.25), p], w=0.25)
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        self.track('/VPAX', [p, R(-8.1, 2.6)], w=0.25)
        self.via('/VPAX', R(-8.1, 2.6), *SV)
        lxb, lxa = pp('L1', '/LXB'), pp('L1', '/LXA')
        self.track('/LXA', [pin(16), R(-3.0, 1.75), (lxa[0], lxa[1] - 0.2)], w=0.25)
        self.track('/LXB', [pin(14), R(-3.0, 0.75), R(-3.3, 1.05), (lxb[0], UY + 1.05), lxb], w=0.25)
        # Bottom row: VBAT to its caps and ferrite; SPI/NRESET to staggered vias.
        vb = [pp(r, '/LR_VBAT') for r in ('C11', 'C12', 'FB1')]
        self.track('/LR_VBAT', [pin(17), vb[0]], w=0.25)
        self.track('/LR_VBAT', [vb[0], vb[2]], w=0.3)
        for ref in ('C11', 'C12'):
            g = pp(ref, 'GND')
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                          (23, '/LR_SCK', 4.45), (24, '/LR_NSS', 3.55)):
            p = pin(n)
            sig(net, [p, (p[0], UY + y)])
        sig('/LR_BUSY', [pin(25), R(2.7, 1.75), R(2.7, 3.4)])

    def usb_c(self):
        """Join the duplicated USB-C pads (the autorouter cannot thread the 0.5 mm pitch)."""
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
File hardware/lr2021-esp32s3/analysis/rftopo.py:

import re, json, collections, sys
import networkx as nx
from networkx.algorithms import isomorphism as iso

def parse_ref(path):
    t = open(path).read()
    comps = {}
    for m in re.finditer(r'\n\t\(footprint "([^"]+)"(.*?)\n\t\)', t, re.S):
        blk = m.group(2)
        ref = re.search(r'\(property "Reference" "([^"]+)"', blk).group(1)
        val = re.search(r'\(property "ALTIUM_VALUE" "([^"]*)"', blk)
        val = val.group(1) if val else re.search(r'\(property "Value" "([^"]*)"', blk).group(1)
        pads = {}
        for pm in re.finditer(r'\(pad "([^"]*)"(.*?)\n\t\t\)', blk, re.S):
            n = re.search(r'\(net "([^"]*)"\)', pm.group(2))
            if n and pm.group(1): pads.setdefault(pm.group(1), n.group(1))
        comps[ref] = (val, pads)
    return comps

def parse_ours(path):
    import subprocess
    out = subprocess.run(['/usr/bin/python3', '-c', f'''
import pcbnew, json
b=pcbnew.LoadBoard("{path}")
d={{}}
for f in b.GetFootprints():
    pads={{}}
    for p in f.Pads():
        if p.GetNumber(): pads.setdefault(p.GetNumber(), p.GetNetname())
    d[f.GetReference()]=(f.GetValue(), pads, bool(f.IsDNP()))
print(json.dumps(d))
'''], capture_output=True, text=True).stdout
    d = json.loads(out.strip().splitlines()[-1])
    return {k: (('NC' if v[2] else v[0]), v[1]) for k, v in d.items()}

def norm(v):
    v = v.strip().replace('µ', 'u').replace(' ', '')
    if v.upper() in ('NC', 'DNP', 'NF', 'N/C'): return 'NC'
    m = re.match(r'^([0-9.]+)(p|n|u)?(F|H)?$', v, re.I)
    if m:
        num = float(m.group(1)); unit = (m.group(2) or '').lower(); kind = (m.group(3) or '').upper()
        return f'{num:g}{unit}{kind}'
    return v

def build(comps, chip, ants, gndnames):
    pinrole = {'1': 'VR_PA', '27': 'RFO_LF', '28': 'RFO_LF', '29': 'RFI_LF', '31': 'RFI_HF', '32': 'RFO_HF'}
    netlabel = {}
    for p, role in pinrole.items():
        netlabel[comps[chip][1][p]] = role
    for a, lab in ants.items():
        netlabel[comps[a][1]['1']] = lab
    for g in gndnames: netlabel[g] = 'GND'
    # adjacency: nets -> two-terminal passives
    two = {r: c for r, c in comps.items() if r[0] in 'LCDF' and len(c[1]) == 2 and not r.startswith('FB')}
    netcomp = collections.defaultdict(set)
    for r, (v, pads) in two.items():
        for n in pads.values(): netcomp[n].add(r)
    start = [comps[chip][1][p] for p in pinrole]
    seen_n, seen_c, todo = set(), set(), list(start)
    while todo:
        n = todo.pop()
        if n in seen_n: continue
        seen_n.add(n)
        if netlabel.get(n) in ('GND',) : continue
        for r in netcomp[n]:
            if r in seen_c: continue
            seen_c.add(r)
            for m in two[r][1].values():
                if m not in seen_n: todo.append(m)
    G = nx.Graph()
    for n in seen_n: G.add_node(('n', n), kind='n', label=netlabel.get(n, 'net'))
    for r in seen_c:
        v, pads = two[r]
        G.add_node(('c', r), kind='c', label=r[0] + ':' + norm(v))
        for m in pads.values():
            G.add_edge(('c', r), ('n', m))
    return G

ref = parse_ref(sys.argv[1]); ours = parse_ours(sys.argv[2])
gr = build(ref, 'U1', {'ANT_LF1': 'ANT_LF', 'ANT_HF1': 'ANT_HF'}, ['GND'])
go = build(ours, 'U6', {'J5': 'ANT_LF', 'J6': 'ANT_HF'}, ['GND'])
print('reference RF graph:', sum(1 for n in gr if n[0]=='c'), 'components', sum(1 for n in gr if n[0]=='n'), 'nets')
print('our RF graph      :', sum(1 for n in go if n[0]=='c'), 'components', sum(1 for n in go if n[0]=='n'), 'nets')
gm = iso.GraphMatcher(gr, go, node_match=lambda a, b: a['label'] == b['label'])
if gm.is_isomorphic():
    print('TOPOLOGY + VALUES: IDENTICAL (graph isomorphic with matching labels)')
    for a, b in sorted(gm.mapping.items()):
        if a[0] == 'c': print(f'   ref {a[1]:6} -> ours {b[1]:6} {gr.nodes[a]["label"]}')
else:
    print('NOT isomorphic; label multisets:')
    ca = collections.Counter(d['label'] for _, d in gr.nodes(data=True)); cb = collections.Counter(d['label'] for _, d in go.nodes(data=True))
    print('  only in ref :', dict(ca - cb)); print('  only in ours:', dict(cb - ca))
    # topology without values: parts by type (L/C/D), nets by role
    gm2 = iso.GraphMatcher(gr, go, node_match=lambda a, b: a['kind'] == b['kind'] and (
        a['label'][0] == b['label'][0] if a['kind'] == 'c' else a['label'] == b['label']))
    print('  topology only (types, no values) isomorphic:', gm2.is_isomorphic())

print('\n--- second pass: diodes compared by type only ---')
for G in (gr, go):
    for n, d in G.nodes(data=True):
        if d['label'].startswith('D:'): d['label'] = 'D'
gm = iso.GraphMatcher(gr, go, node_match=lambda a, b: a['label'] == b['label'])
print('isomorphic with all L/C values and net roles matching:', gm.is_isomorphic())
if gm.is_isomorphic():
    m = gm.mapping
    pairs = sorted((a[1], b[1], gr.nodes[a]['label']) for a, b in m.items() if a[0] == 'c')
    for a, b, lab in pairs: print(f'   ref {a:7} -> ours {b:6} {lab}')
    roles = sorted((gr.nodes[a]['label'], a[1], b[1]) for a, b in m.items() if a[0] == 'n' and gr.nodes[a]['label'] != 'net')
    for lab, a, b in roles: print(f'   net role {lab:7}: ref {a:22} -> ours {b}')
